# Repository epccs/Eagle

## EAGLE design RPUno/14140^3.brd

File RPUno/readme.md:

[RPUno]

This circuit board started with solar power but turned into a somewhat general purpose control board, it has an ATmega328p like an Arduino Uno. Some of the input-output pins are level shifted to work with onboard current sources that make for some interesting possibilities.

[RPUno]: https://github.com/epccs/RPUno/

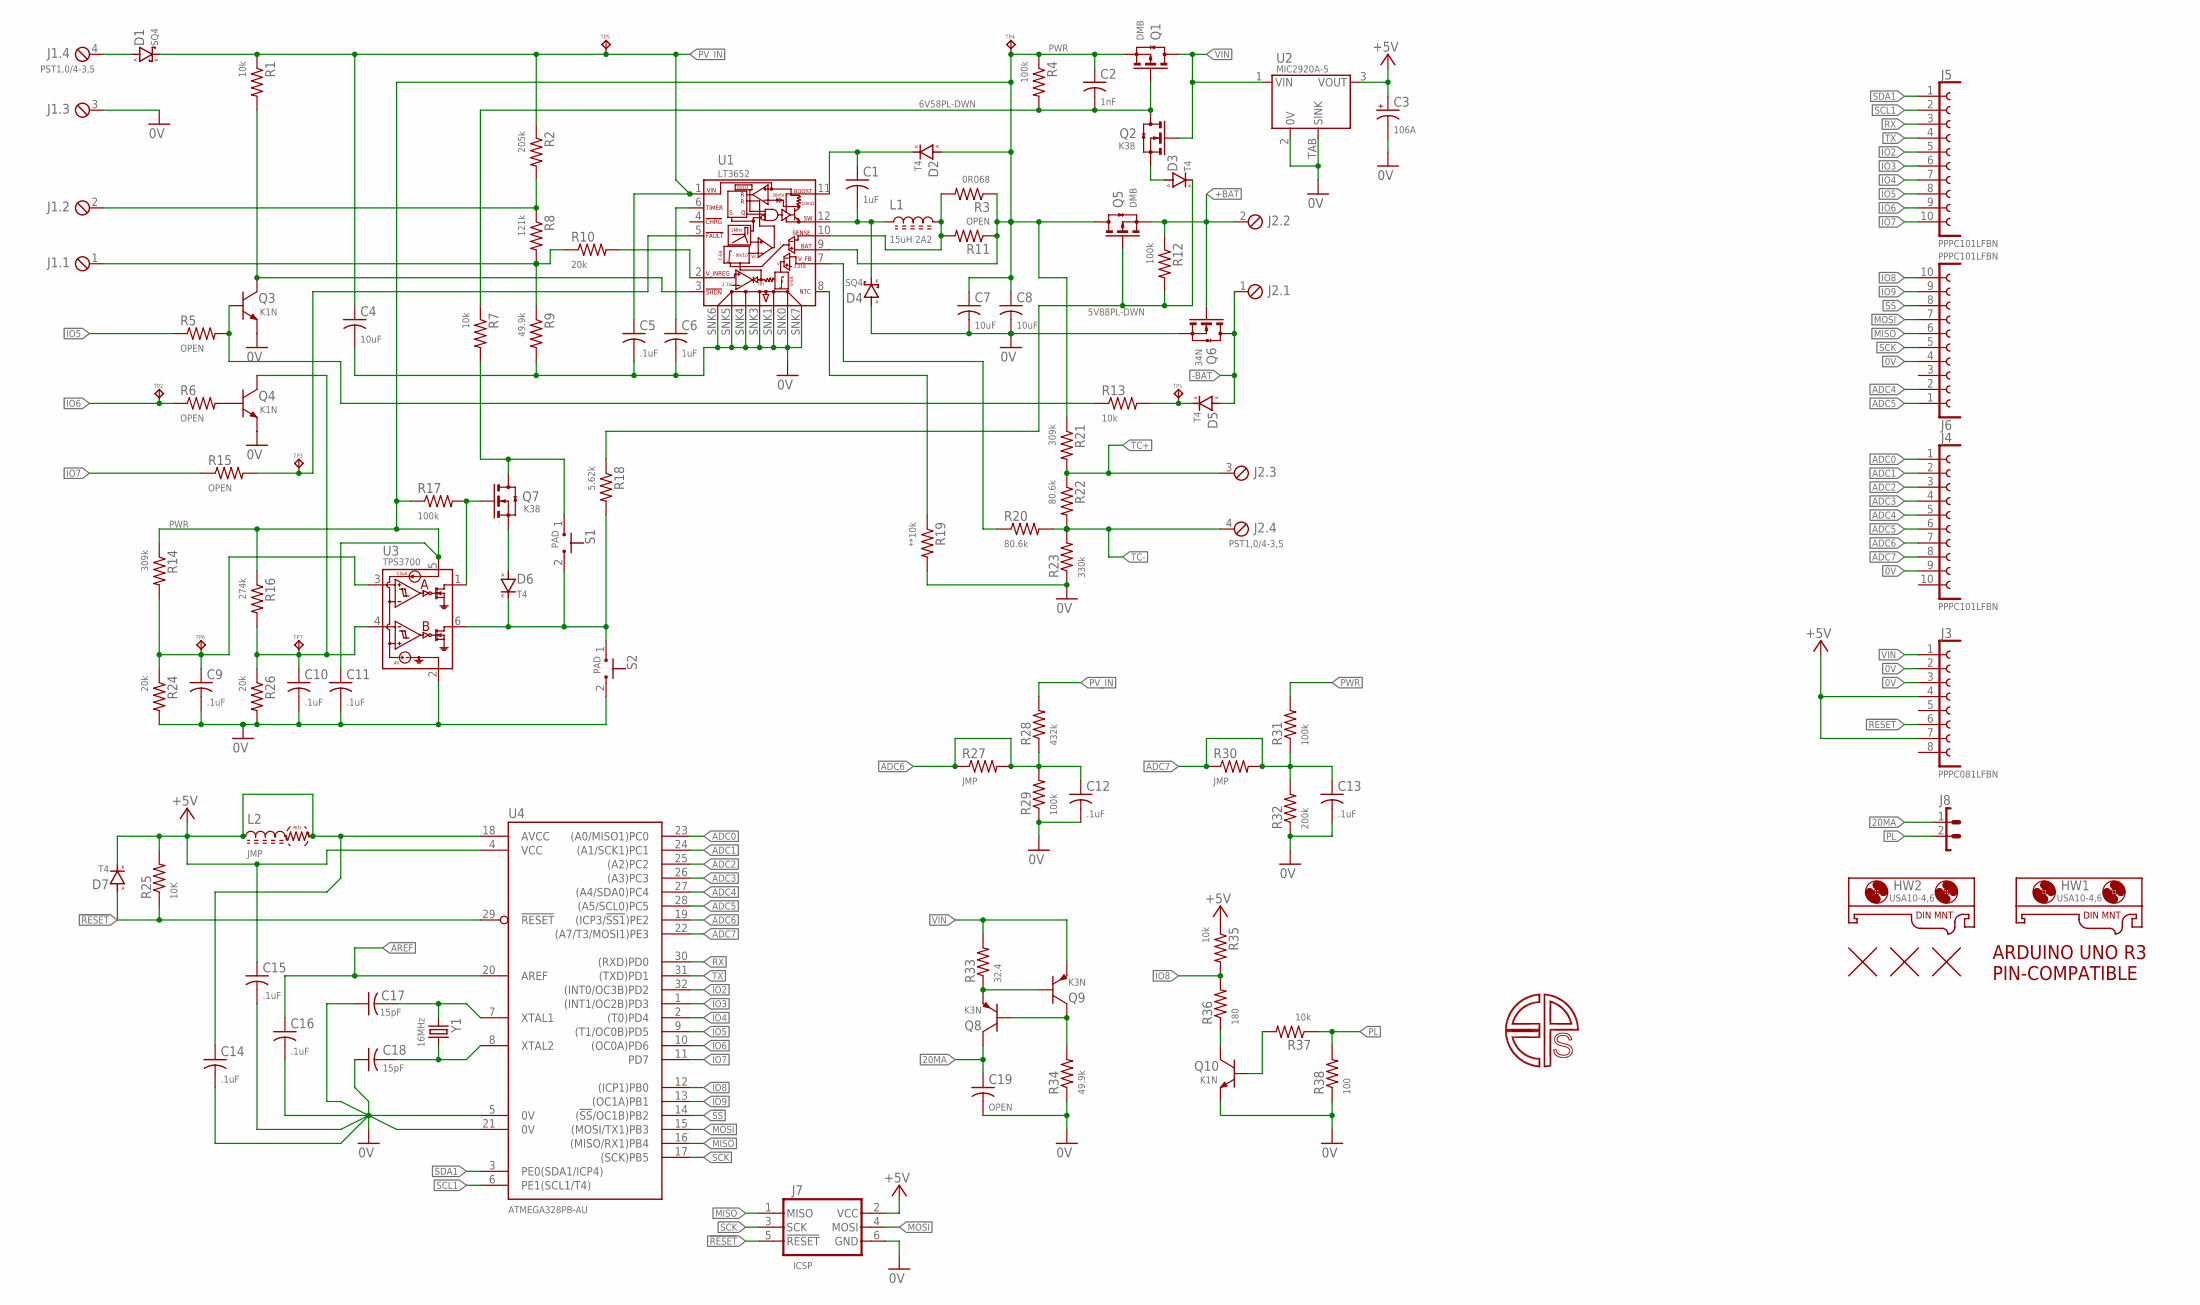
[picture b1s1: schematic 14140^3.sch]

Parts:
C1, C6: 1uF; C0805(2012)
C2: 1nF; C0603(1608)
C3: 106A; 3216
C4, C7, C8: 10uF; C1206(3216)
C5: .1uF; C0805(2012)
C9, C10, C11, C12, C13, C14, C15, C16: .1uF; C0603(1608)
C17, C18: 15pF; C0603(1608)
C19: OPEN; C0805(2012)
D1, D4: SQ4; SMA
D2, D3, D5, D6, D7: T4; SOD123
HW1, HW2: USA10-4,6; USA10
J1, J2: PST1,0/4-3,5; MCV4
J3: PPPC081LFBN; F1X8
J4, J5, J6: PPPC101LFBN; F1X10
J7: ICSP; ISP
J8: 1X2
L1: 15uH 2A2; L3939
L2: JMP; C0805(2012)
Q1, Q5: DMB; SOT23
Q2, Q7: K38; SOT23
Q3, Q4, Q10: K1N; SOT23
Q6: 34N; SOT23
Q8, Q9: K3N; SOT23
R1, R7, R13, R35, R37: 10k; C0805(2012)
R2: 205k; C0805(2012)
R3: 0R068; C1210(3225)
R4, R12, R17, R29, R31: 100k; C0805(2012)
R5, R6, R15: OPEN; C0805(2012)
R8: 121k; C0805(2012)
R9, R34: 49.9k; C0805(2012)
R10, R24, R26: 20k; C0805(2012)
R11: OPEN; C1210(3225)
R14, R21: 309k; C0805(2012)
R16: 274k; C0805(2012)
R18: 5.62k; C0805(2012)
R19: **10k; C0805(2012)
R20, R22: 80.6k; C0805(2012)
R23: 330k; C0805(2012)
R25: 10K; C0805(2012)
R27, R30: JMP; C0805(2012)
R28: 432k; C0805(2012)
R32: 200k; C0805(2012)
R33: 32.4; C0805(2012)
R36: 180; C0805(2012)
R38: 100; C0805(2012)
S1, S2: PAD; C0805(2012)
TP1, TP2, TP3, TP4, TP5, TP6, TP7: TPPAD1-08; P1-08
U1: LT3652; 12MSOP-EDP-HAND
U2: MIC2920A-5; SOT223
U3: TPS3700; SOT23-6
U4: ATMEGA328PB-AU; TQFP32-08
U$1: ARDUINO-UNO; ARDUINO_UNO
U$2, U$3, U$4: FIDUCIAL1.27; FIDUCIAL-1.27
Y1: 16MHz; CSM-3X

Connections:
0V: C3.-, C4.2, C5.2, C6.2, C7.2, C8.2, C9.2, C10.2, C11.2, C12.2, C13.2, C14.2, C15.2, C16.2, C17.1, C18.1, C19.2, D4.A, J1.3, J3.2, J3.3, J4.9, J6.4, J7.6 (GND), Q3.E, Q4.E, Q6.2(S) (S), Q10.E, R9.2, R19.2, R23.1, R24.2, R26.2, R29.1, R32.1, R34.1, R38.1, S2.2 (3), U1.SNK0 (0V), U1.SNK1 (0V), U1.SNK3 (0V), U1.SNK4 (0V), U1.SNK5 (0V), U1.SNK6 (0V), U1.SNK7 (0V), U2.2 (0V), U2.TAB (SINK), U3.2 (0V), U4.5 (0V), U4.21 (0V)
5V88PL-DWN: D3.C (K), Q5.1(G) (G), R12.2, R18.1
6V58PL-DWN: C2.2, Q1.1(G) (G), Q2.3(D) (D), R4.2, R7.1
20MA: C19.1, J8.1, Q8.C
!FAULT: R15.2, TP3.TP, U1.5 (!FAULT)
!RESET!: D7.A, J3.6, J7.5 (!RESET), R25.1, U4.29 (!RESET)
!SS: J6.8, U4.14 ((!SS!/OC1B)PB2)
+5V: C3.+, C14.1, C15.1, D7.C (K), J3.4, J3.7, J7.2 (VCC), L2.1, L2.2, R25.2, R35.1, U2.3 (VOUT), U4.4 (VCC), U4.18 (AVCC)
+BAT: J2.2, Q5.2(S) (S), Q6.1(G) (G), R12.1
-BAT: D5.A, J2.1, Q6.3(D) (D)
ADC0: J4.1, U4.23 ((A0/MISO1)PC0)
ADC1: J4.2, U4.24 ((A1/SCK1)PC1)
ADC2: J4.3, U4.25 ((A2)PC2)
ADC3: J4.4, U4.26 ((A3)PC3)
ADC4: J4.5, J6.2, U4.27 ((A4/SDA0)PC4)
ADC5: J4.6, J6.1, U4.28 ((A5/SCL0)PC5)
ADC6: C12.1, J4.7, R27.1, R27.2, R28.1, R29.2, U4.19 ((ICP3/!SS1!)PE2)
ADC7: C13.1, J4.8, R30.1, R30.2, R31.1, R32.2, U4.22 ((A7/T3/MOSI1)PE3)
AREF: C16.1, U4.20 (AREF)
IO2: J5.5, U4.32 ((INT0/OC3B)PD2)
IO3: J5.6, U4.1 ((INT1/OC2B)PD3)
IO4: J5.7, U4.2 ((T0)PD4)
IO5: J5.8, R5.1, U4.9 ((T1/OC0B)PD5)
IO6: J5.9, R6.1, TP2.TP, U4.10 ((OC0A)PD6)
IO7: J5.10, R15.1, U4.11 (PD7)
IO8: J6.10, R35.2, R36.2, U4.12 ((ICP1)PB0)
IO9: J6.9, U4.13 ((OC1A)PB1)
MISO: J6.6, J7.1 (MISO), U4.16 ((MISO/RX1)PB4)
MOSI: J6.7, J7.4 (MOSI), U4.15 ((MOSI/TX1)PB3)
unnamed: C6.1, U1.6 (TIMER)
unnamed: R20.1, U1.7 (V_FB)
unnamed: J1.1, R8.2, R9.1, R10.1
unnamed: Q3.C, R1.2, U1.3 (!SHDN)
unnamed: D1.A, J1.4
unnamed: Q4.B, R6.2
unnamed: C10.1, Q4.C, R16.2, R26.1, TP7.TP, U3.4 (INB)
unnamed: D3.A, Q2.2(S) (S)
unnamed: J1.2, R2.2, R8.1
unnamed: C1.1, D2.C (K), U1.11 (BOOST)
unnamed: R10.2, U1.2 (V_INREG)
unnamed: Q8.E, Q9.B, R33.1
unnamed: D5.C (K), R13.2, TP1.TP
unnamed: D6.A, Q7.2(S) (S)
unnamed: C9.1, R14.2, R24.1, TP6.TP, U3.3 (INA)
unnamed: Q7.1(G) (G), R17.2, U3.1 (OUTA)
unnamed: D6.C (K), R18.2, S1.2 (3), S2.1, U3.6 (OUTB)
unnamed: Q7.3(D) (D), R7.2, S1.1
unnamed: Q8.B, Q9.C, R34.2
unnamed: Q10.B, R37.2
unnamed: Q10.C, R36.1
unnamed: Q3.B, R5.2, R13.1
unnamed: C17.2, U4.7 (XTAL1), Y1.1
unnamed: C18.2, U4.8 (XTAL2), Y1.2
NTC1: R19.1, U1.8 (NTC)
PL: J8.2, R37.1, R38.2
PV_IN: C4.1, C5.1, D1.K, R1.1, R2.1, R28.2, TP5.TP, U1.1 (VIN)
PWR: C2.1, C7.1, C8.1, C11.1, D2.A, Q1.2(S) (S), Q5.3(D) (D), R3.1, R4.1, R11.1, R14.1, R16.1, R17.1, R21.1, R31.2, TP4.TP, U1.9 (BAT), U3.5 (VDD)
RX: J5.3, U4.30 ((RXD)PD0)
SCK: J6.5, J7.3 (SCK), U4.17 ((SCK)PB5)
SCL1: J5.2, U4.6 (PE1(SCL1/T4))
SDA1: J5.1, U4.3 (PE0(SDA1/ICP4))
SENSE: L1.2, R3.2, R11.2, U1.10 (SENSE)
SW: C1.2, D4.K, L1.1, U1.12 (SW)
TC+: J2.3, R21.2, R22.1
TC-: J2.4, R20.2, R22.2, R23.2
TX: J5.4, U4.31 ((TXD)PD1)
VIN: J3.1, Q1.3(D) (D), Q2.1(G) (G), Q9.E, R33.2, U2.1 (VIN)

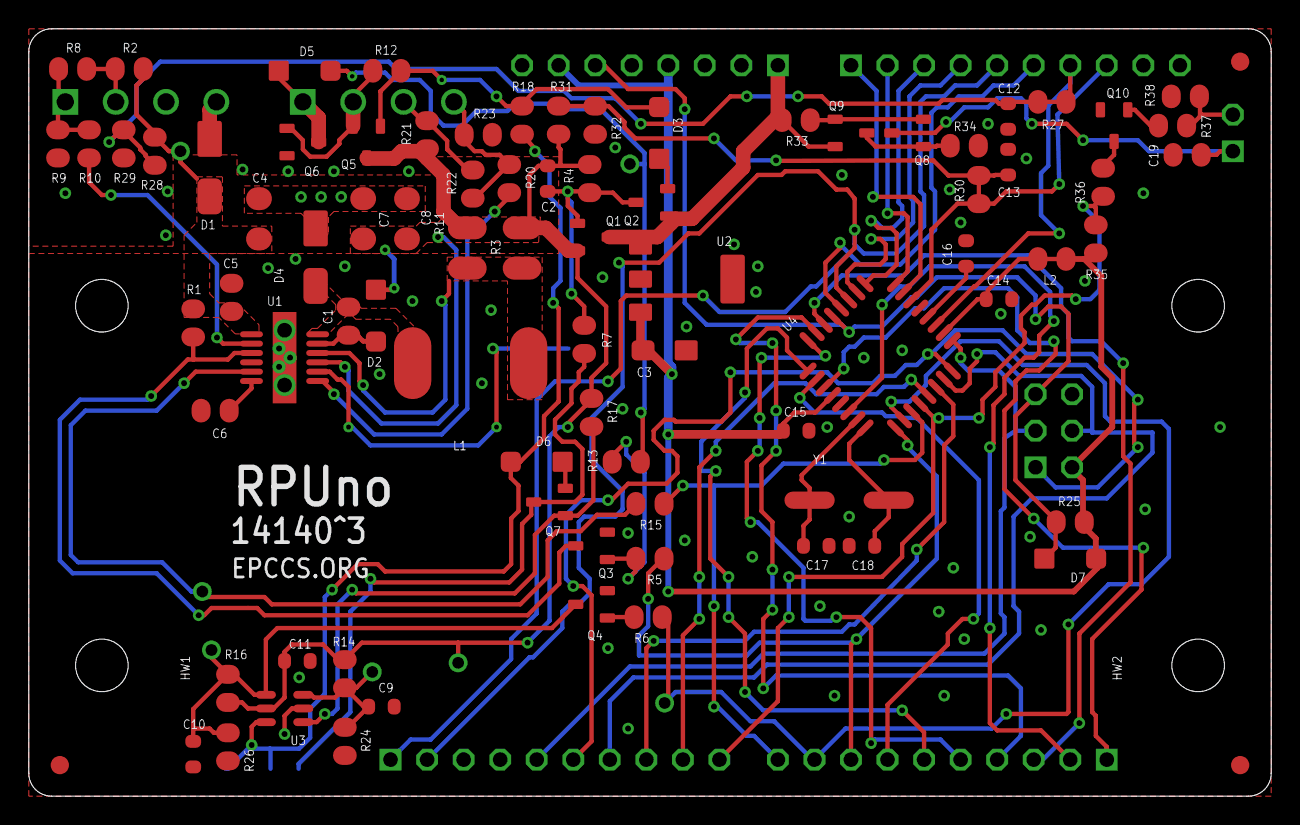
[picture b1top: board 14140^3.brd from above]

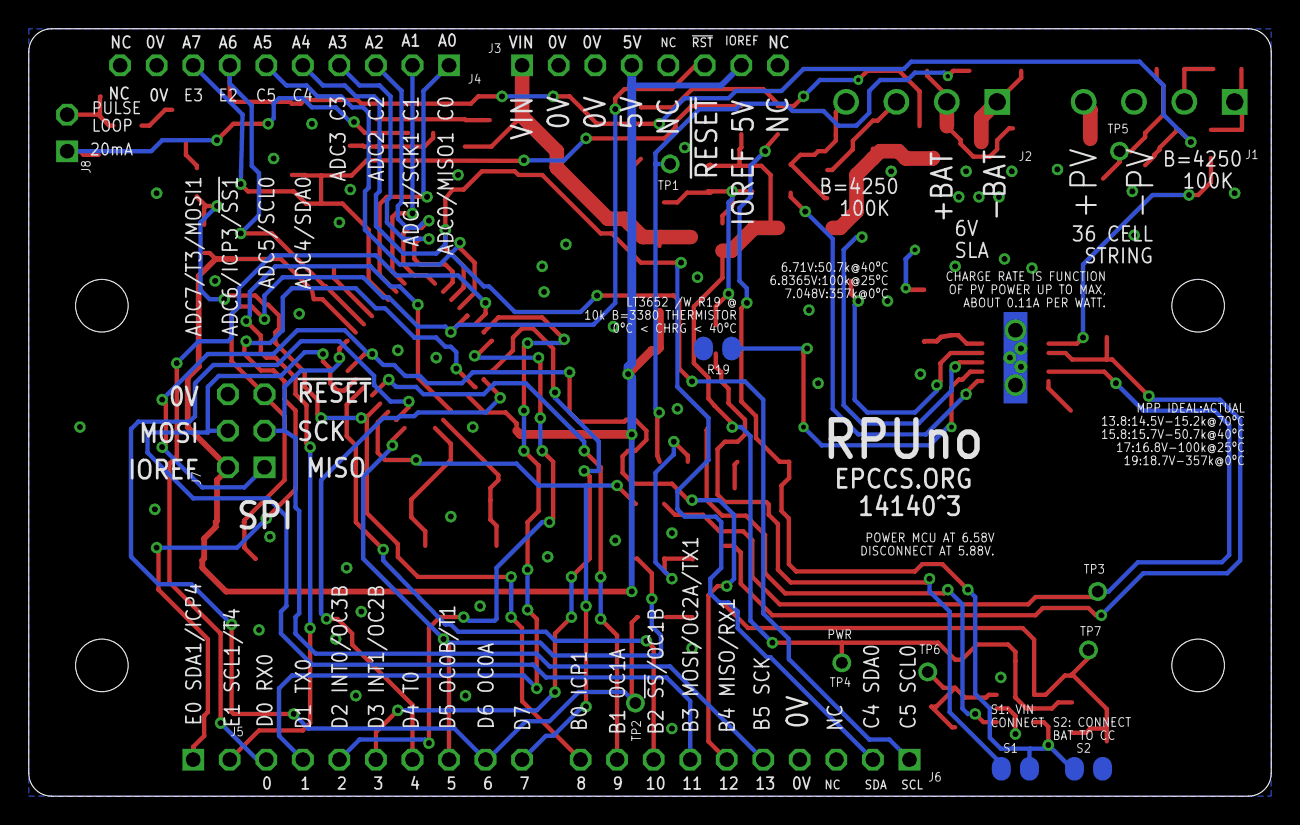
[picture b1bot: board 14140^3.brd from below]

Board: 2 copper layers, 86.4 x 53.3 mm, 104 parts (19 on the bottom side), 67 nets.

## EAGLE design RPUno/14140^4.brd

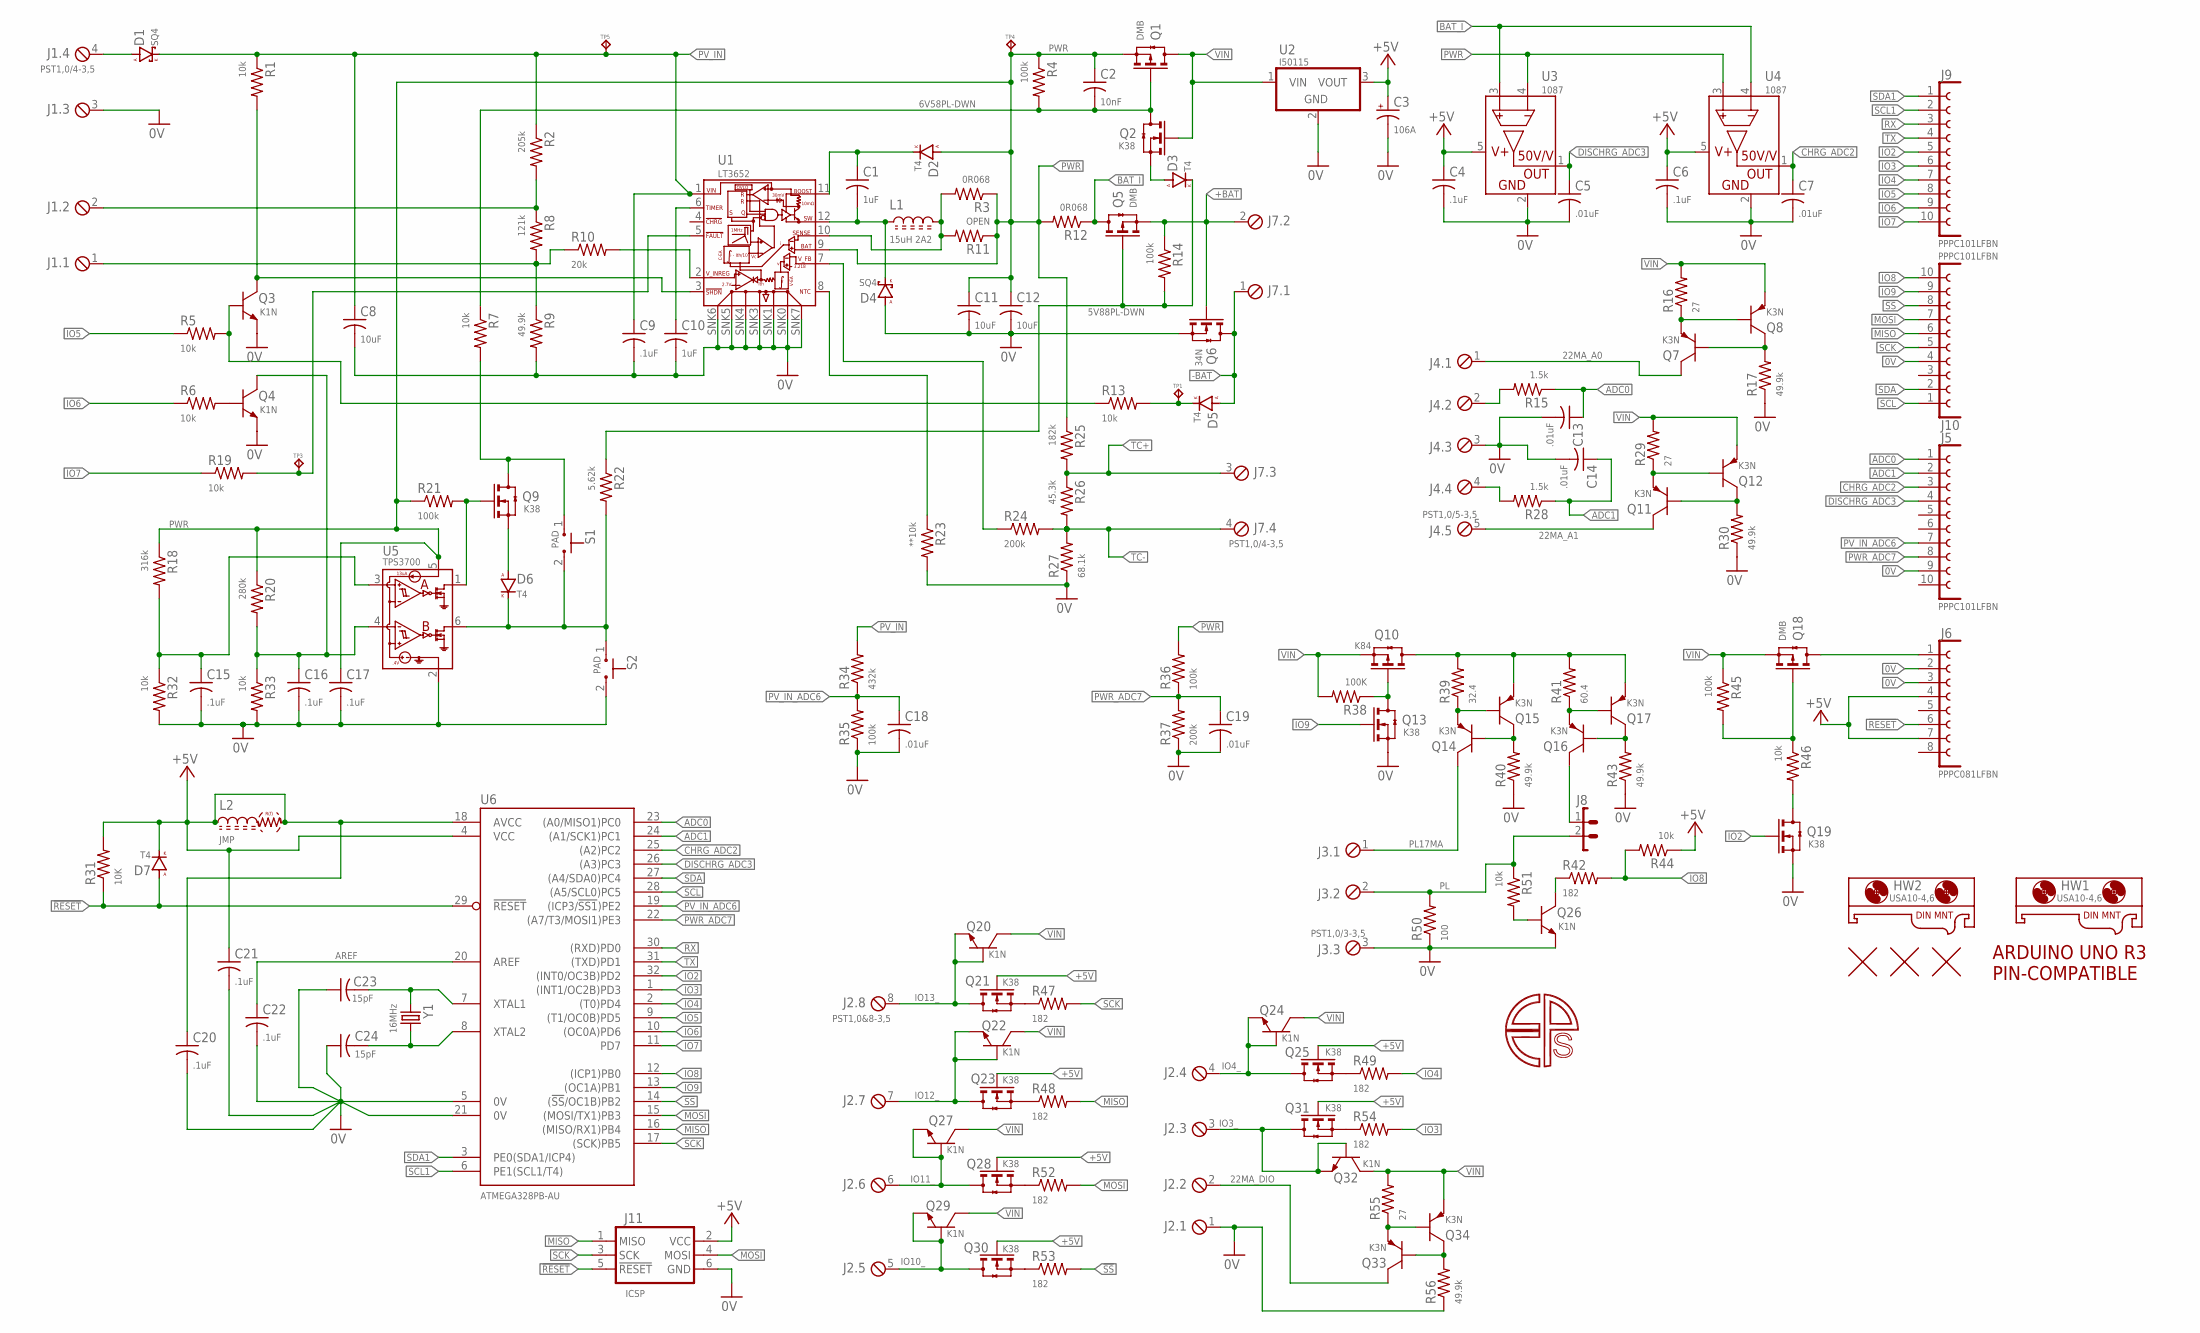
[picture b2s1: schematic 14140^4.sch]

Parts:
C1, C10: 1uF; C0805(2012)
C2: 10nF; C0603(1608)
C3: 106A; 3216
C4, C6, C15, C16, C17, C20, C21, C22: .1uF; C0603(1608)
C5, C7, C13, C14, C18, C19: .01uF; C0603(1608)
C8, C11, C12: 10uF; C1206(3216)
C9: .1uF; C0805(2012)
C23, C24: 15pF; C0603(1608)
D1, D4: SQ4; SMA
D2, D3, D5, D6, D7: T4; SOD123
HW1, HW2: USA10-4,6; USA10
J1, J7: PST1,0/4-3,5; MCV4
J2: PST1,0&8-3,5; MCV8
J3: PST1,0/3-3,5; MCV3
J4: PST1,0/5-3,5; MCV5
J5, J9, J10: PPPC101LFBN; F1X10
J6: PPPC081LFBN; F1X8
J8: 1X2
J11: ICSP; ISP
L1: 15uH 2A2; L3939
L2: JMP; C0805(2012)
Q1, Q5, Q18: DMB; SOT23
Q2, Q9, Q13, Q19, Q21, Q23, Q25, Q28, Q30, Q31: K38; SOT23
Q3, Q4, Q20, Q22, Q24, Q26, Q27, Q29, Q32: K1N; SOT23
Q6: 34N; SOT23
Q7, Q8, Q11, Q12, Q14, Q15, Q16, Q17, Q33, Q34: K3N; SOT23
Q10: K84; SOT23
R1, R5, R6, R7, R13, R19, R32, R33, R44, R46, R51: 10k; C0805(2012)
R2: 205k; C0805(2012)
R3, R12: 0R068; C1210(3225)
R4, R14, R21, R35, R36, R45: 100k; C0805(2012)
R8: 121k; C0805(2012)
R9, R17, R30, R40, R43, R56: 49.9k; C0805(2012)
R10: 20k; C0805(2012)
R11: OPEN; C1210(3225)
R15, R28: 1.5k; C0805(2012)
R16, R29, R55: 27; C0805(2012)
R18: 316k; C0805(2012)
R20: 280k; C0805(2012)
R22: 5.62k; C0805(2012)
R23: **10k; C0805(2012)
R24, R37: 200k; C0805(2012)
R25: 182k; C0805(2012)
R26: 45.3k; C0805(2012)
R27: 68.1k; C0805(2012)
R31: 10K; C0805(2012)
R34: 432k; C0805(2012)
R38: 100K; C0805(2012)
R39: 32.4; C0805(2012)
R41: 60.4; C0805(2012)
R42, R47, R48, R49, R52, R53, R54: 182; C0805(2012)
R50: 100; C0805(2012)
S1, S2: PAD; C0805(2012)
TP1, TP3, TP4, TP5: TPPAD1-08; P1-08
U1: LT3652; 12MSOP-EDP-HAND
U2: I50115; OKI-78SR-H
U3, U4: 1087; SOT23-5
U5: TPS3700; SOT23-6
U6: ATMEGA328PB-AU; TQFP32-08
U$1: ARDUINO-UNO; ARDUINO_UNO
U$2, U$3, U$4: FIDUCIAL1.27; FIDUCIAL-1.27
Y1: 16MHz; CSM-3X

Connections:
0V: C3.-, C4.2, C5.2, C6.2, C7.2, C8.2, C9.2, C10.2, C11.2, C12.2, C13.2, C14.2, C15.2, C16.2, C17.2, C18.2, C19.2, C20.2, C21.2, C22.2, C23.1, C24.1, D4.A, J1.3, J2.1, J3.3, J4.3, J5.9, J6.2, J6.3, J10.4, J11.6 (GND), Q3.E, Q4.E, Q6.2(S) (S), Q13.2(S) (S), Q19.2(S) (S), Q26.E, R9.2, R17.1, R23.2, R27.1, R30.1, R32.2, R33.2, R35.1, R37.1, R40.1, R43.1, R50.1, R56.1, S2.2 (3), U1.SNK0 (0V), U1.SNK1 (0V), U1.SNK3 (0V), U1.SNK4 (0V), U1.SNK5 (0V), U1.SNK6 (0V), U1.SNK7 (0V), U2.2 (GND), U3.2 (GND), U4.2 (GND), U5.2 (0V), U6.5 (0V), U6.21 (0V)
5V88PL-DWN: D3.C (K), Q5.1(G) (G), R14.2, R22.1
6V58PL-DWN: C2.2, Q1.1(G) (G), Q2.3(D) (D), R4.2, R7.1
22MA_A0: J4.1, Q7.C
22MA_A1: J4.5, Q11.C
22MA_DIO: J2.2, Q33.C
!FAULT: R19.2, TP3.TP, U1.5 (!FAULT)
!RESET!: D7.A, J6.6, J11.5 (!RESET), R31.1, U6.29 (!RESET)
!SS: J10.8, R53.2, U6.14 ((!SS!/OC1B)PB2)
+5V: C3.+, C4.1, C6.1, C20.1, C21.1, D7.C (K), J6.4, J6.7, J11.2 (VCC), L2.1, L2.2, Q21.1(G) (G), Q23.1(G) (G), Q25.1(G) (G), Q28.1(G) (G), Q30.1(G) (G), Q31.1(G) (G), R31.2, R44.1, U2.3 (VOUT), U3.5 (VCC), U4.5 (VCC), U6.4 (VCC), U6.18 (AVCC)
+BAT: J7.2, Q5.2(S) (S), Q6.1(G) (G), R14.1
-BAT: D5.A, J7.1, Q6.3(D) (D)
ADC0: C13.1, J5.1, R15.1, U6.23 ((A0/MISO1)PC0)
ADC1: C14.1, J5.2, R28.1, U6.24 ((A1/SCK1)PC1)
AREF: C22.1, U6.20 (AREF)
BAT_I: Q5.3(D) (D), R12.1, U3.3 (S+), U4.4 (S-)
CHRG_ADC2: C7.1, J5.3, U4.1 (OUT), U6.25 ((A2)PC2)
DISCHRG_ADC3: C5.1, J5.4, U3.1 (OUT), U6.26 ((A3)PC3)
IO2: J9.5, Q19.1(G) (G), U6.32 ((INT0/OC3B)PD2)
IO3: J9.6, R54.2, U6.1 ((INT1/OC2B)PD3)
IO3_: J2.3, Q31.3(D) (D), Q32.B, Q32.E
IO4: J9.7, R49.2, U6.2 ((T0)PD4)
IO4_: J2.4, Q24.B, Q24.E, Q25.3(D) (D)
IO5: J9.8, R5.1, U6.9 ((T1/OC0B)PD5)
IO6: J9.9, R6.1, U6.10 ((OC0A)PD6)
IO7: J9.10, R19.1, U6.11 (PD7)
IO8: J10.10, R42.2, R44.2, U6.12 ((ICP1)PB0)
IO9: J10.9, Q13.1(G) (G), U6.13 ((OC1A)PB1)
IO10_: J2.5, Q29.B, Q29.E, Q30.3(D) (D)
IO11_: J2.6, Q27.B, Q27.E, Q28.3(D) (D)
IO12_: J2.7, Q22.B, Q22.E, Q23.3(D) (D)
IO13_: J2.8, Q20.B, Q20.E, Q21.3(D) (D)
MISO: J10.6, J11.1 (MISO), R48.2, U6.16 ((MISO/RX1)PB4)
MOSI: J10.7, J11.4 (MOSI), R52.2, U6.15 ((MOSI/TX1)PB3)
unnamed: C10.1, U1.6 (TIMER)
unnamed: R24.1, U1.7 (V_FB)
unnamed: J1.1, R8.2, R9.1, R10.1
unnamed: Q3.C, R1.2, U1.3 (!SHDN)
unnamed: D1.A, J1.4
unnamed: Q4.B, R6.2
unnamed: C16.1, Q4.C, R20.2, R33.1, U5.4 (INB)
unnamed: D3.A, Q2.2(S) (S)
unnamed: J1.2, R2.2, R8.1
unnamed: C1.1, D2.C (K), U1.11 (BOOST)
unnamed: R10.2, U1.2 (V_INREG)
unnamed: Q10.3(D) (D), Q15.E, Q17.E, R39.2, R41.2
unnamed: D5.C (K), R13.2, TP1.TP
unnamed: D6.A, Q9.2(S) (S)
unnamed: C15.1, R18.2, R32.1, U5.3 (INA)
unnamed: Q9.1(G) (G), R21.2, U5.1 (OUTA)
unnamed: D6.C (K), R22.2, S1.2 (3), S2.1, U5.6 (OUTB)
unnamed: Q9.3(D) (D), R7.2, S1.1
unnamed: J8.1, Q16.C
unnamed: Q7.E, Q8.B, R16.1
unnamed: Q23.2(S) (S), R48.1
unnamed: Q28.2(S) (S), R52.1
unnamed: Q7.B, Q8.C, R17.2
unnamed: J4.2, R15.2
unnamed: Q10.1(G) (G), Q13.3(D) (D), R38.1
unnamed: Q30.2(S) (S), R53.1
unnamed: J4.4, R28.2
unnamed: Q11.E, Q12.B, R29.1
unnamed: Q11.B, Q12.C, R30.2
unnamed: Q33.E, Q34.B, R55.1
unnamed: Q31.2(S) (S), R54.1
unnamed: Q25.2(S) (S), R49.1
unnamed: Q33.B, Q34.C, R56.2
unnamed: Q21.2(S) (S), R47.1
unnamed: Q18.1(G) (G), R45.2, R46.1
unnamed: J6.1, Q18.3(D) (D)
unnamed: Q19.3(D) (D), R46.2
unnamed: Q3.B, R5.2, R13.1
unnamed: Q26.B, R51.2
unnamed: Q26.C, R42.1
unnamed: Q14.E, Q15.B, R39.1
unnamed: C23.2, U6.7 (XTAL1), Y1.1
unnamed: C24.2, U6.8 (XTAL2), Y1.2
unnamed: Q14.B, Q15.C, R40.2
unnamed: Q16.E, Q17.B, R41.1
unnamed: Q16.B, Q17.C, R43.2
NTC1: R23.1, U1.8 (NTC)
PL: J3.2, J8.2, R50.2, R51.1
PL17MA: J3.1, Q14.C
PV_IN: C8.1, C9.1, D1.K, R1.1, R2.1, R34.2, TP5.TP, U1.1 (VIN)
PV_IN_ADC6: C18.1, J5.7, R34.1, R35.2, U6.19 ((ICP3/!SS1!)PE2)
PWR: C2.1, C11.1, C12.1, C17.1, D2.A, Q1.2(S) (S), R3.1, R4.1, R11.1, R12.2, R18.1, R20.1, R21.1, R25.1, R36.2, TP4.TP, U1.9 (BAT), U3.4 (S-), U4.3 (S+), U5.5 (VDD)
PWR_ADC7: C19.1, J5.8, R36.1, R37.2, U6.22 ((A7/T3/MOSI1)PE3)
RX: J9.3, U6.30 ((RXD)PD0)
SCK: J10.5, J11.3 (SCK), R47.2, U6.17 ((SCK)PB5)
SCL: J10.1, U6.28 ((A5/SCL0)PC5)
SCL1: J9.2, U6.6 (PE1(SCL1/T4))
SDA: J10.2, U6.27 ((A4/SDA0)PC4)
SDA1: J9.1, U6.3 (PE0(SDA1/ICP4))
SENSE: L1.2, R3.2, R11.2, U1.10 (SENSE)
SW: C1.2, D4.K, L1.1, U1.12 (SW)
TC+: J7.3, R25.2, R26.1
TC-: J7.4, R24.2, R26.2, R27.2
TX: J9.4, U6.31 ((TXD)PD1)
VIN: Q1.3(D) (D), Q2.1(G) (G), Q8.E, Q10.2(S) (S), Q12.E, Q18.2(S) (S), Q20.C, Q22.C, Q24.C, Q27.C, Q29.C, Q32.C, Q34.E, R16.2, R29.2, R38.2, R45.1, R55.2, U2.1 (VIN)

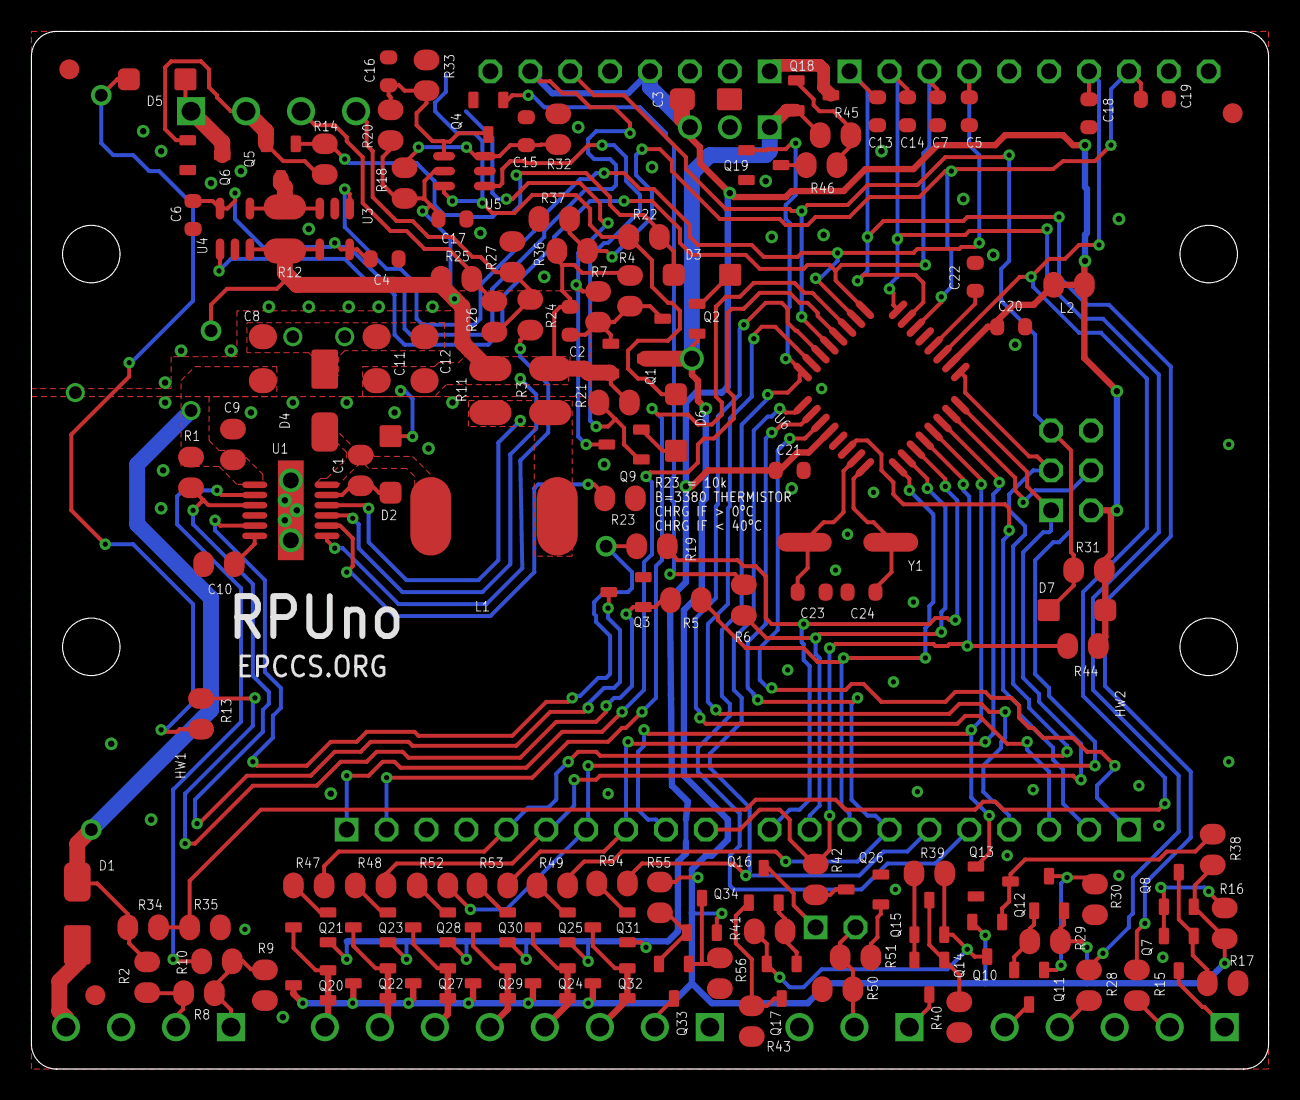
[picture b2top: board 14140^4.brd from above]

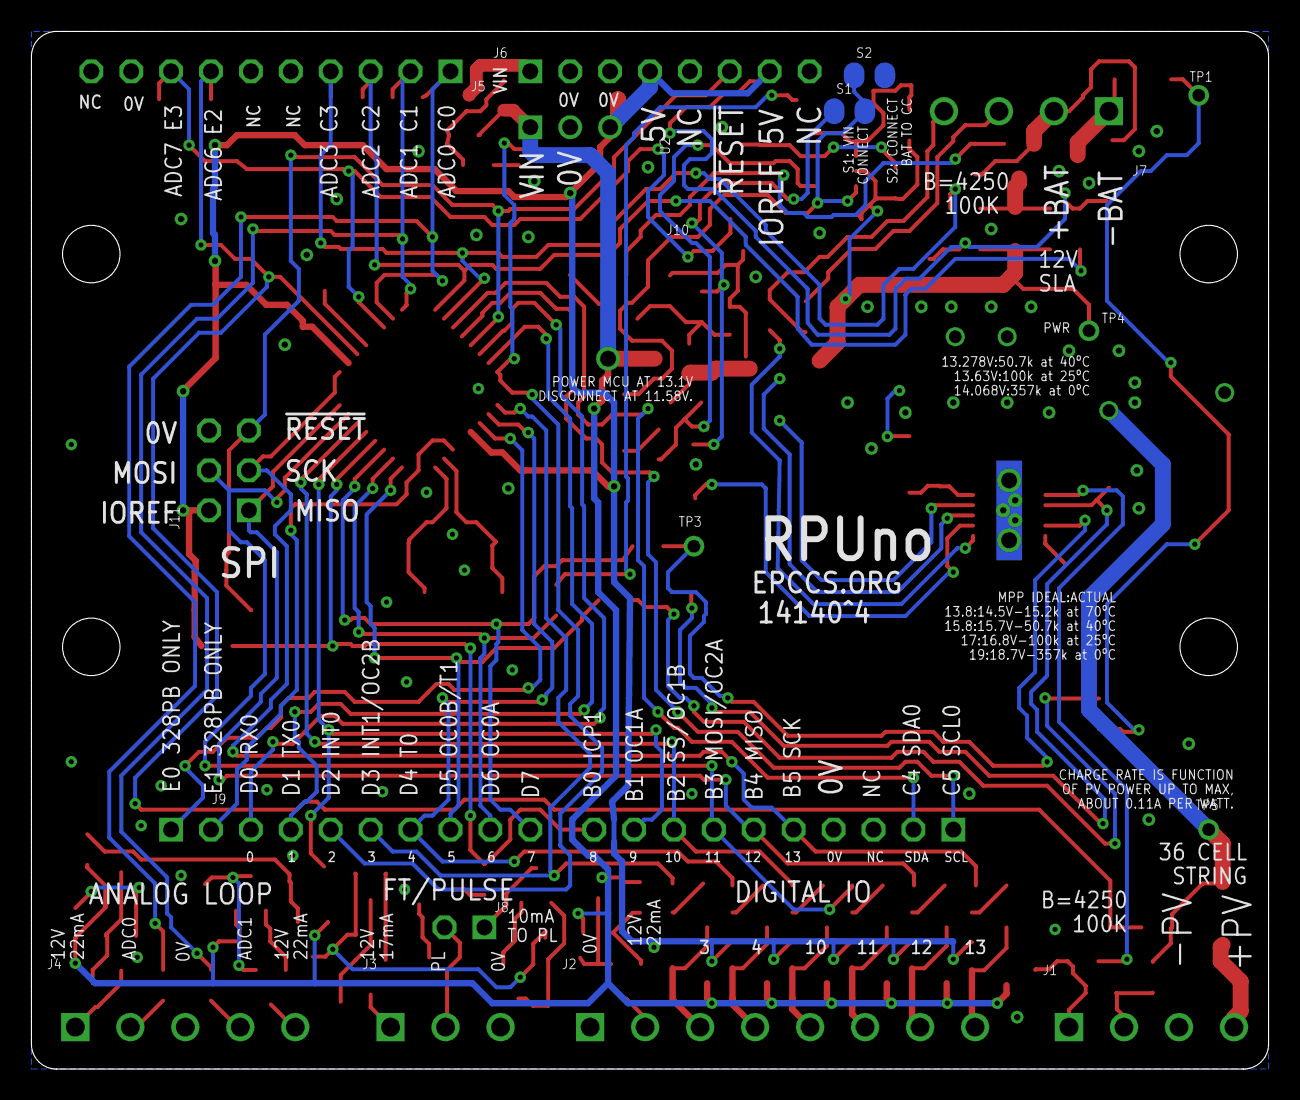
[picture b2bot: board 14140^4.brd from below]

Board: 2 copper layers, 78.7 x 66.0 mm, 153 parts (19 on the bottom side), 99 nets.

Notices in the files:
parts and their libraries:
J-BoardHDR: Copyright (C) 2013 Ronald Steven Sutherland
Released under the Creative Commons
Attribution Share-Alike 3.0 License
http://creativecommons.org/licenses/by-sa/3.0
H-Fiducial: under the terms of the GNU Free Documentation License, Version 1.2 or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
J-TP: Copyright (C) 2015 Ronald Sutherland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
